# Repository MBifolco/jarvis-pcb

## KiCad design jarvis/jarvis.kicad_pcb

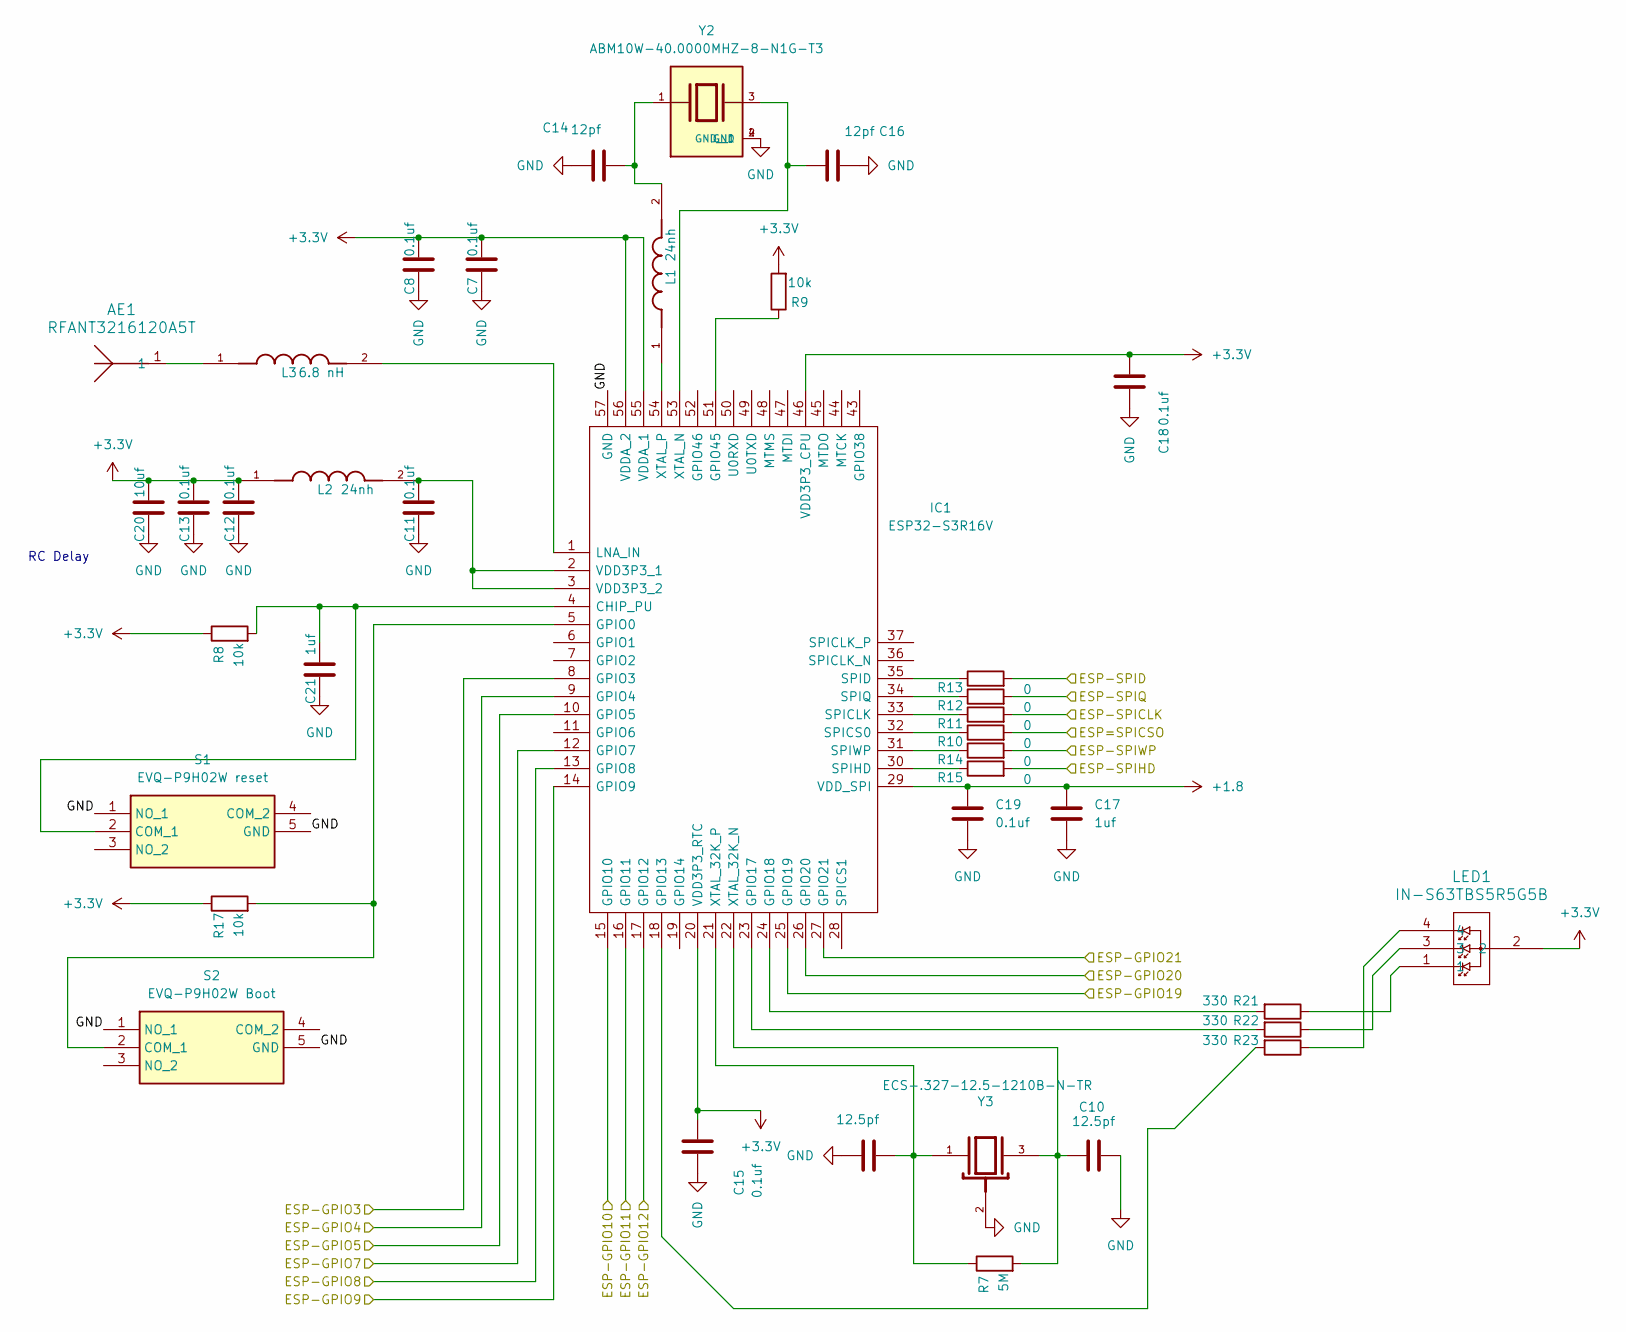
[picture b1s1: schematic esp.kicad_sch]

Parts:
AE1: RFANT3216120A5T; ANT_RFANT3216120A5T_WAL
C7, C8, C11, C12, C13, C15, C19: 0.1uf; C_0603_1608Metric
C9, C10: 12.5pf; C_0402_1005Metric
C14, C16: 12pf; C_0402_1005Metric
C17, C21: 1uf; C_0603_1608Metric
C18: 0.1uf; C_0402_1005Metric
C20: 10uf; C_0603_1608Metric
IC1: ESP32-S3R16V; esp32-s3r16v; Manufacturer_Part_Number ESP32-S3R16V; Mouser Part Number 356-ESP32-S3R16V
L1, L2: 24nh; MLG1005SR24JT000
L3: 6.8 nH; MLG1005SR24JT000
LED1: IN-S63TBS5R5G5B; IN-S63TBS5R5G5B_INO
R7: 5M; R_0603_1608Metric
R8, R9, R17: 10k; R_0603_1608Metric
R10, R11, R12, R13, R14, R15: 0; R_0603_1608Metric
R21, R22, R23: 330; R_0603_1608Metric
S1: EVQ-P9H02W reset; EVQP9H02W; Manufacturer_Part_Number EVQ-P9H02W; Mouser Part Number 667-EVQ-P9H02W
S2: EVQ-P9H02W Boot; EVQP9H02W; Manufacturer_Part_Number EVQ-P9H02W; Mouser Part Number 667-EVQ-P9H02W
Y2: ABM10W-40.0000MHZ-8-N1G-T3; XTAL_ABM10W-40.0000MHZ-8-N1G-T3; PARTREV 10.06.2020
Y3: ECS-.327-12.5-1210B-N-TR; XTAL_ECS-.327-12.5-1210B-N-TR

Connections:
+1.8: C17.2, C19.2, IC1.29 (VDD_SPI); also elsewhere on the board
+3.3V: C7.1, C8.1, C12.1, C13.1, C15.1, C18.1, C20.1, IC1.20 (VDD3P3_RTC), IC1.46 (VDD3P3_CPU), IC1.55 (VDDA_1), IC1.56 (VDDA_2), L2.1, LED1.2, R8.1, R9.2, R17.1; also elsewhere on the board
/Components/AMP-BCLK: IC1.9 (GPIO4); also elsewhere on the board
/Components/AMP-DIN: IC1.8 (GPIO3); also elsewhere on the board
/Components/AMP-LRCLK: IC1.10 (GPIO5); also elsewhere on the board
/Components/FLASH-CLK: R11.2; also elsewhere on the board
/Components/FLASH-CS: R10.2; also elsewhere on the board
/Components/FLASH-DI_IO0: R13.2; also elsewhere on the board
/Components/FLASH-DO_IO1: R12.2; also elsewhere on the board
/Components/FLASH-HOLD: R15.2; also elsewhere on the board
/Components/FLASH-WP_IO2: R14.2; also elsewhere on the board
/Components/MIC-BCK: IC1.12 (GPIO7); also elsewhere on the board
/Components/MIC-DATA: IC1.14 (GPIO9); also elsewhere on the board
/Components/MIC-WS: IC1.13 (GPIO8); also elsewhere on the board
/ESP/ESP-GPIO10: IC1.15 (GPIO10); also elsewhere on the board
/ESP/ESP-GPIO11: IC1.16 (GPIO11); also elsewhere on the board
/ESP/ESP-GPIO12: IC1.17 (GPIO12); also elsewhere on the board
/ESP/ESP-GPIO19: IC1.25 (GPIO19); also elsewhere on the board
/ESP/ESP-GPIO20: IC1.26 (GPIO20); also elsewhere on the board
/ESP/ESP-GPIO21: IC1.27 (GPIO21)
GND: C7.2, C8.2, C9.2, C10.2, C11.2, C12.2, C13.2, C14.1, C15.2, C16.2, C17.1, C18.2, C19.1, C20.2, C21.2, IC1.57 (GND), S1.1 (NO_1), S1.5 (GND), S2.1 (NO_1), S2.5 (GND), Y2.2 (GND), Y2.4 (GND__1), Y3.2; also elsewhere on the board
unnamed: AE1.1, L3.1
unnamed: C14.2, L1.2, Y2.1
unnamed: C21.1, IC1.4 (CHIP_PU), R8.2, S1.2 (COM_1)
unnamed: IC1.5 (GPIO0), R17.2, S2.2 (COM_1)
unnamed: IC1.18 (GPIO13), R23.2
unnamed: IC1.23 (GPIO17), R22.2
unnamed: IC1.24 (GPIO18), R21.2
unnamed: IC1.51 (GPIO45), R9.1
unnamed: IC1.1 (LNA_IN), L3.2
unnamed: IC1.33 (SPICLK), R11.1
unnamed: IC1.32 (SPICS0), R10.1
unnamed: IC1.35 (SPID), R13.1
unnamed: IC1.30 (SPIHD), R15.1
unnamed: IC1.34 (SPIQ), R12.1
unnamed: IC1.31 (SPIWP), R14.1
unnamed: C11.1, IC1.2 (VDD3P3_1), IC1.3 (VDD3P3_2), L2.2
unnamed: C10.1, IC1.22 (XTAL_32K_N), R7.2, Y3.3
unnamed: C9.1, IC1.21 (XTAL_32K_P), R7.1, Y3.1
unnamed: C16.1, IC1.53 (XTAL_N), Y2.3
unnamed: IC1.54 (XTAL_P), L1.1
unnamed: LED1.1, R21.1
unnamed: LED1.3, R22.1
unnamed: LED1.4, R23.1

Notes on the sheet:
RC Delay

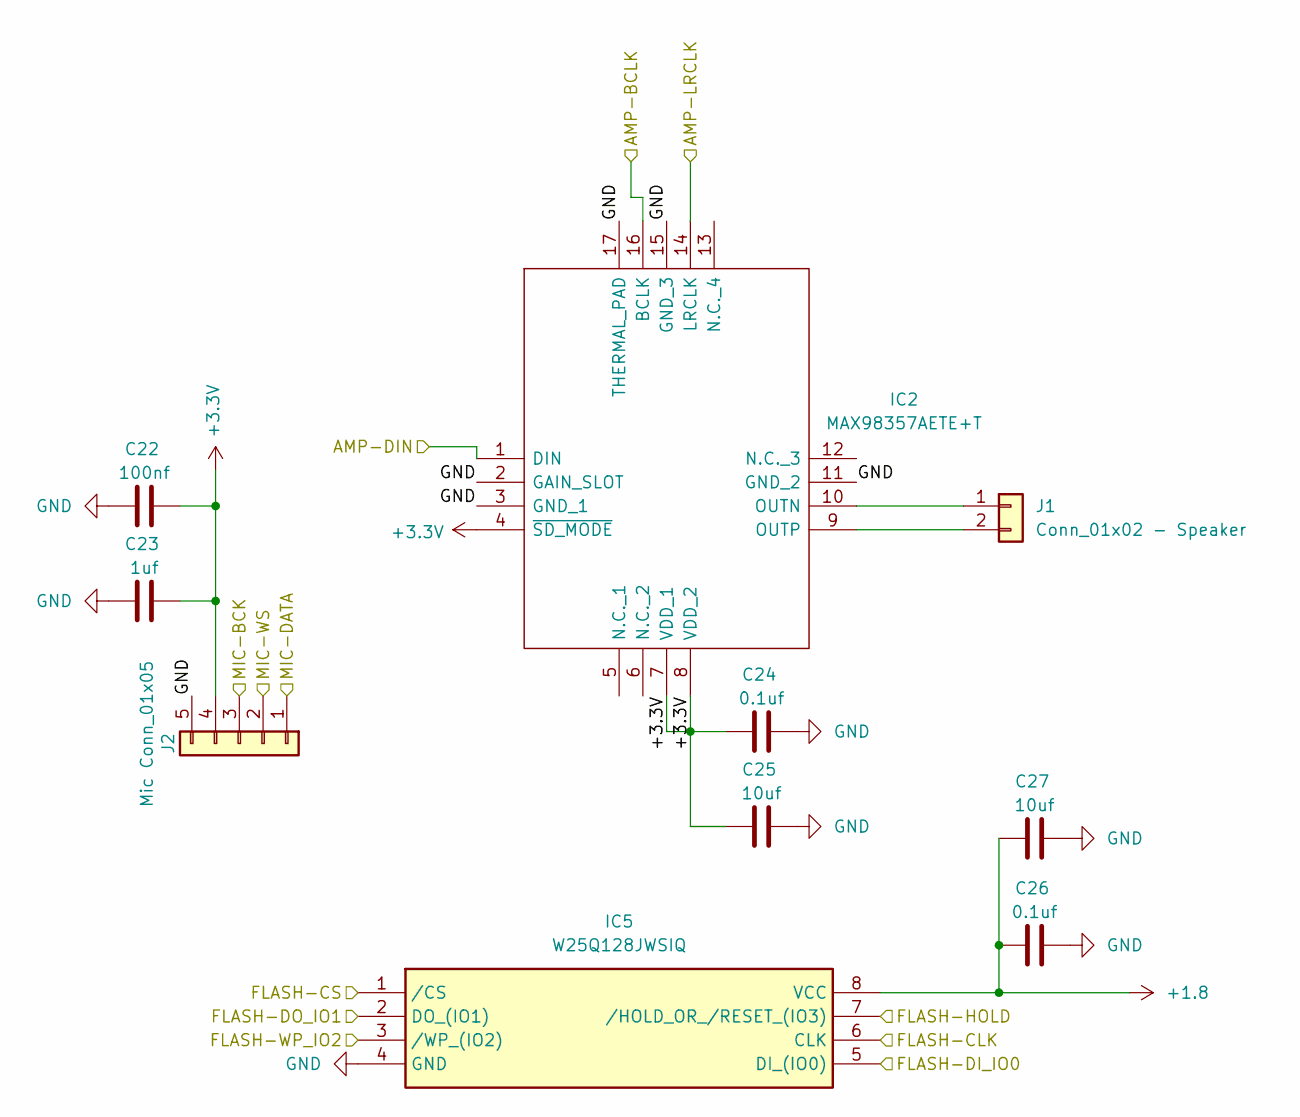
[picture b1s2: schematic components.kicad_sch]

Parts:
C22: 100nf; C_0603_1608Metric
C23: 1uf; C_0603_1608Metric
C24, C26: 0.1uf; C_0603_1608Metric
C25, C27: 10uf; C_0603_1608Metric
IC2: MAX98357AETE+T; LIB_MAX98357AETE+T; Manufacturer_Part_Number MAX98357AETE+T; Mouser Part Number 700-MAX98357AETE+T
IC5: W25Q128JWSIQ; W25Q128JWSIQ-1.8; Manufacturer_Part_Number W25Q128JWSIQ; Mouser Part Number 454-W25Q128JWSIQ
J1: Conn_01x02 - Speaker; Molex_PicoBlade_53047-0210_1x02_P1.25mm_Vertical
J2: Mic Conn_01x05; Molex_PicoBlade_53047-0510_1x05_P1.25mm_Vertical

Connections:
+1.8: C26.2, C27.2, IC5.8 (VCC); also elsewhere on the board
+3.3V: C22.1, C23.1, C24.2, C25.2, IC2.4 (~SD_MODE), IC2.7 (VDD_1), IC2.8 (VDD_2), J2.4; also elsewhere on the board
/Components/AMP-BCLK: IC2.16 (BCLK); also elsewhere on the board
/Components/AMP-DIN: IC2.1 (DIN); also elsewhere on the board
/Components/AMP-LRCLK: IC2.14 (LRCLK); also elsewhere on the board
/Components/FLASH-CLK: IC5.6 (CLK); also elsewhere on the board
/Components/FLASH-CS: IC5.1 (/CS); also elsewhere on the board
/Components/FLASH-DI_IO0: IC5.5 (DI_(IO0)); also elsewhere on the board
/Components/FLASH-DO_IO1: IC5.2 (DO_(IO1)); also elsewhere on the board
/Components/FLASH-HOLD: IC5.7 (/HOLD_OR_/RESET_(IO3)); also elsewhere on the board
/Components/FLASH-WP_IO2: IC5.3 (/WP_(IO2)); also elsewhere on the board
/Components/MIC-BCK: J2.3; also elsewhere on the board
/Components/MIC-DATA: J2.1; also elsewhere on the board
/Components/MIC-WS: J2.2; also elsewhere on the board
GND: C22.2, C23.2, C24.1, C25.1, C26.1, C27.1, IC2.2 (GAIN_SLOT), IC2.3 (GND_1), IC2.11 (GND_2), IC2.15 (GND_3), IC2.17 (THERMAL_PAD), IC5.4 (GND), J2.5; also elsewhere on the board
unnamed: IC2.10 (OUTN), J1.1
unnamed: IC2.9 (OUTP), J1.2

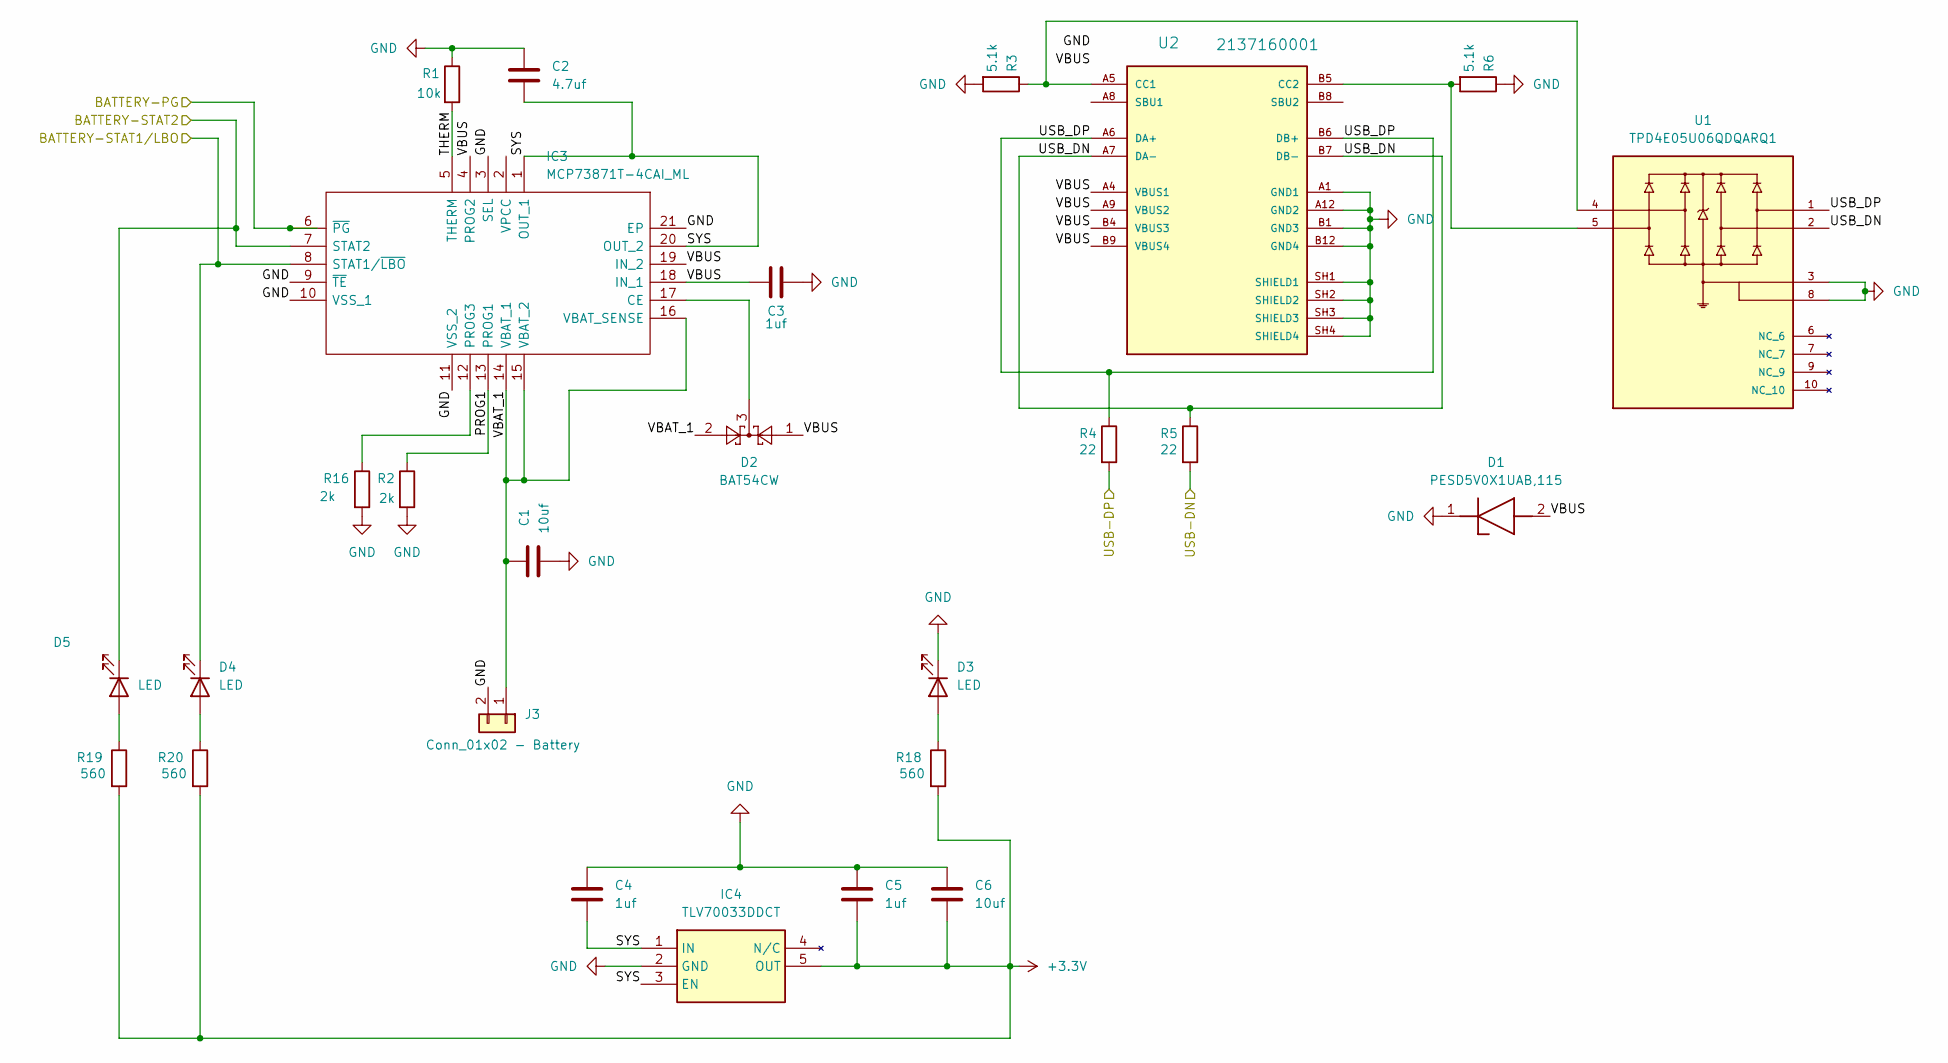
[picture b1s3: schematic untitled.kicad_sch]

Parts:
C1, C6: 10uf; C_0603_1608Metric
C2: 4.7uf; C_0603_1608Metric
C3, C4, C5: 1uf; C_0603_1608Metric
D1: PESD5V0X1UAB,115; PESD5V0X1UAB115; Manufacturer_Part_Number PESD5V0X1UAB,115; Mouser Part Number 771-PESD5V0X1UAB115
D2: BAT54CW; SOT-323_SC-70_Handsoldering
D3, D4, D5: LED; LED_0603_1608Metric
IC3: MCP73871T-4CAI_ML; MCP73871T-4CAI ML; Manufacturer_Part_Number MCP73871T-4CAI/ML; Mouser Part Number 579-MCP73871T4CAIML
IC4: TLV70033DDCT; Manufacturer_Part_Number TLV70033DDCT; Mouser Part Number 595-TLV70033DDCT
J3: Conn_01x02 - Battery; Molex_PicoBlade_53047-0210_1x02_P1.25mm_Vertical
R1: 10k; R_0603_1608Metric
R2, R16: 2k; R_0603_1608Metric
R3, R6: 5.1k; R_0603_1608Metric
R4, R5: 22; R_0603_1608Metric
R18, R19, R20: 560; R_0603_1608Metric
U1: TPD4E05U06QDQARQ1; IC_TPD4E05U06QDQARQ1; PARTREV F
U2: 2137160001; MOLEX_2137160001-holes; PARTREV B

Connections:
+3.3V: C5.2, C6.2, IC4.5 (OUT), R18.2, R19.2, R20.2; also elsewhere on the board
/ESP/ESP-GPIO10: D4.1 (K), IC3.8 (STAT1/~LBO); also elsewhere on the board
/ESP/ESP-GPIO11: D5.1 (K), IC3.7 (STAT2); also elsewhere on the board
/ESP/ESP-GPIO12: IC3.6 (~PG); also elsewhere on the board
/ESP/ESP-GPIO19: R4.2; also elsewhere on the board
/ESP/ESP-GPIO20: R5.2; also elsewhere on the board
/Power/PROG1: IC3.13 (PROG1), R2.1
/Power/SYS: C2.2, C4.2, IC3.1 (OUT_1), IC3.20 (OUT_2), IC4.1 (IN), IC4.3 (EN)
/Power/THERM: IC3.5 (THERM), R1.2
/Power/VBAT_1: C1.1, D2.2, IC3.14 (VBAT_1), IC3.15 (VBAT_2), IC3.16 (VBAT_SENSE), J3.1
/Power/VBUS: C3.1, D1.2 (A), D2.1, IC3.4 (PROG2), IC3.18 (IN_1), IC3.19 (IN_2), U2.A4 (VBUS1), U2.A9 (VBUS2), U2.B4 (VBUS3), U2.B9 (VBUS4)
GND: C1.2, C2.1, C3.2, C4.1, C5.1, C6.1, D1.1 (K), D3.1 (K), IC3.3 (SEL), IC3.9 (~TE), IC3.10 (VSS_1), IC3.11 (VSS_2), IC3.21 (EP), IC4.2 (GND), J3.2, R1.1, R2.2, R3.2, R6.1, R16.2, U1.3, U1.8, U2.A1 (GND1), U2.A12 (GND2), U2.B1 (GND3), U2.B12 (GND4), U2.SH1 (SHIELD1), U2.SH2 (SHIELD2), U2.SH3 (SHIELD3), U2.SH4 (SHIELD4); also elsewhere on the board
unnamed: D3.2 (A), R18.1
unnamed: D4.2 (A), R20.1
unnamed: D5.2 (A), R19.1
unnamed: D2.3, IC3.17 (CE)
unnamed: IC3.12 (PROG3), R16.1
unnamed: R3.1, U1.4, U2.A5 (CC1)
unnamed: R6.2, U1.5, U2.B5 (CC2)

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
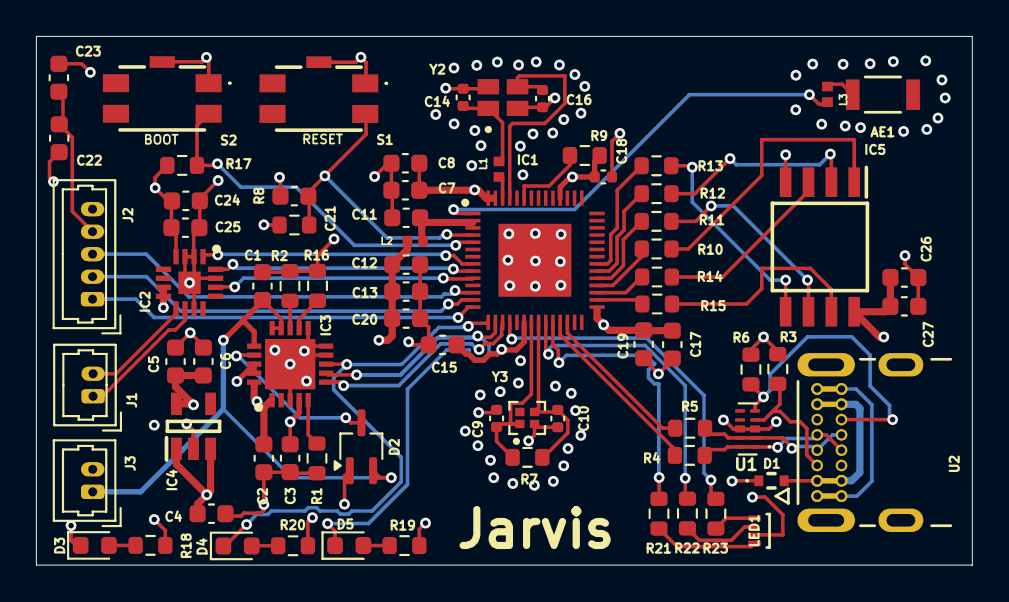
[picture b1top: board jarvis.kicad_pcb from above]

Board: 4 copper layers, 52.0 x 29.4 mm, 74 parts (0 on the bottom side), 59 nets.

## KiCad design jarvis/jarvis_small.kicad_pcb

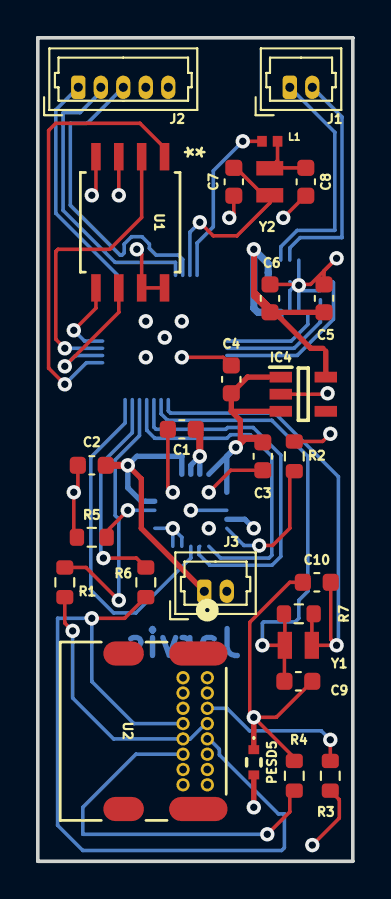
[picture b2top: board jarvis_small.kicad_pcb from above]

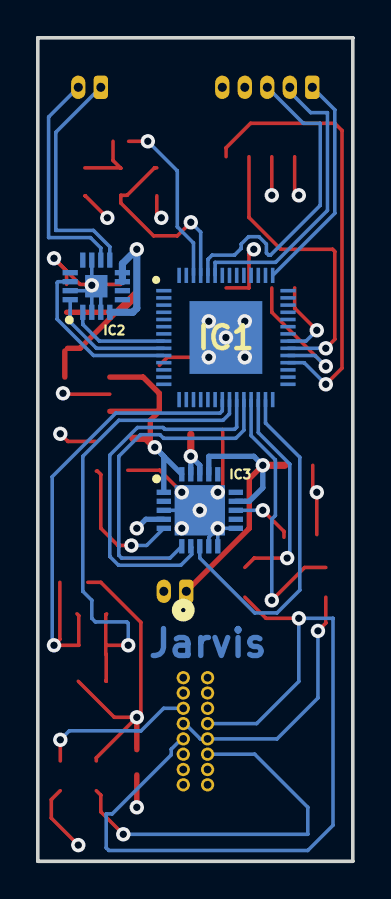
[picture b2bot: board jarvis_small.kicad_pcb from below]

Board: 4 copper layers, 17.5 x 45.8 mm, 30 parts (3 on the bottom side), 32 nets.

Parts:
C1, C4, C5: 1uf; C_0603_1608Metric
C2, C6: 10uf; C_0603_1608Metric
C3: 4.7uf; C_0603_1608Metric
C7, C8, C9, C10: 12pf; C_0603_1608Metric
IC1: ESP32-S3R16V; esp32-s3r16v
IC2: MAX98357AETE+T; LIB_MAX98357AETE+T
IC3: MCP73871T-4CAI_ML; MCP73871T-4CAI ML
IC4: TLV70033DDCT
J1: Conn_01x02 - Speaker; Molex_PicoBlade_53047-0210_1x02_P1.25mm_Vertical
J2: Mic Conn_01x05; Molex_PicoBlade_53047-0510_1x05_P1.25mm_Vertical
J3: Conn_01x02 - Battery; Molex_PicoBlade_53047-0210_1x02_P1.25mm_Vertical
L1: 24nh; MLG1005SR24JT000
PESD5: PESD5V0X1UAB,115; PESD5V0X1UAB115
R1: 2k; R_0603_1608Metric
R2: 10k; R_0603_1608Metric
R3, R4: 5.1k; R_0603_1608Metric
R5, R6: 22; R_0603_1608Metric
R7: 5M; R_0603_1608Metric
U1: W25Q64JVSSIQ
U2: 2137160001; 2137160001_MOL
Y1: Crystal 32.768khz; XTAL_CM8V-T1A-32.768KHZ-7PF-20PPM-TA-QC
Y2: Crystal 40mhz; XTAL_CM8V-T1A-32.768KHZ-7PF-20PPM-TA-QC

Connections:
+3.3V: C5.2, C6.2, IC2.4 (~SD_MODE), IC2.7 (VDD_1), IC2.8 (VDD_2), IC4.5 (OUT), J2.4, U1.3 (/WP(IO2)), U1.7 (/HOLD_OR_/RESET(IO3)), U1.8 (VCC)
/PROG1: IC3.13 (PROG1), R1.1
/SYS: C3.2, C4.2, IC1.32 (SPICS0), IC3.1 (OUT_1), IC3.20 (OUT_2), IC4.1 (IN), IC4.3 (EN), U1.1 (/CS)
/THERM: IC3.5 (THERM), R2.2
/USB_DN: R6.1, U2.A7 (DN1), U2.B7 (DN2)
/USB_DP: R5.1, U2.A6 (DP1), U2.B6 (DP2)
/VBAT_1: C2.1, IC3.14 (VBAT_1), IC3.17 (CE), J3.1
GND: C1.2, C2.2, C3.1, C4.1, C5.1, C6.1, C7.2, C8.1, C9.2, C10.2, IC1.57 (GND), IC2.2 (GAIN_SLOT), IC2.3 (GND_1), IC2.11 (GND_2), IC2.15 (GND_3), IC2.17 (THERMAL_PAD), IC3.3 (SEL), IC3.9 (~TE), IC3.10 (VSS_1), IC3.11 (VSS_2), IC3.21 (EP), IC4.2 (GND), J2.5, J3.2, PESD5.1 (K), R1.2, R2.1, R3.2, R4.1, U1.4 (GND), U2.A1 (GND), U2.A12 (GND), U2.B1 (GND), U2.B12 (GND)
unnamed: C8.2, L1.2, Y2.2
unnamed: IC1.8 (GPIO3), IC2.1 (DIN)
unnamed: IC1.9 (GPIO4), IC2.16 (BCLK)
unnamed: IC1.10 (GPIO5), IC2.14 (LRCLK)
unnamed: IC1.23 (GPIO17), IC3.7 (STAT2)
unnamed: IC1.24 (GPIO18), IC3.6 (~PG)
unnamed: IC1.25 (GPIO19), R5.2
unnamed: IC1.26 (GPIO20), R6.2
unnamed: IC1.27 (GPIO21), IC3.8 (STAT1/~LBO)
unnamed: IC1.43 (GPIO38), J2.1
unnamed: IC1.51 (GPIO45), J2.2
unnamed: IC1.52 (GPIO46), J2.3
unnamed: IC1.33 (SPICLK), U1.6 (CLK)
unnamed: IC1.35 (SPID), U1.5 (DI(IO0))
unnamed: IC1.34 (SPIQ), U1.2 (DO(IO1))
unnamed: C9.1, IC1.22 (XTAL_32K_N), R7.2, Y1.2
unnamed: C10.1, IC1.21 (XTAL_32K_P), R7.1, Y1.1
unnamed: C7.1, IC1.53 (XTAL_N), Y2.1
unnamed: IC1.54 (XTAL_P), L1.1
unnamed: IC2.10 (OUTN), J1.2
unnamed: IC2.9 (OUTP), J1.1
unnamed: R3.1, U2.A5 (CC1)
unnamed: R4.2, U2.B5 (CC2)
VBUS: C1.1, IC3.4 (PROG2), IC3.18 (IN_1), IC3.19 (IN_2), PESD5.2 (A), U2.A4 (VBUS), U2.A9 (VBUS), U2.B9 (VBUS)

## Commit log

2025-06-11 init
2025-06-12 flash routed
2025-06-13 start crystal layout
2025-06-15 crystals done
2025-06-15 initial all connections
2025-06-16 details
2025-08-04 with leds and boot button
2025-08-11 small fixes from testing new pcb swap d lines connected pins on power ic that needed to be changed rbg led to be common anode
